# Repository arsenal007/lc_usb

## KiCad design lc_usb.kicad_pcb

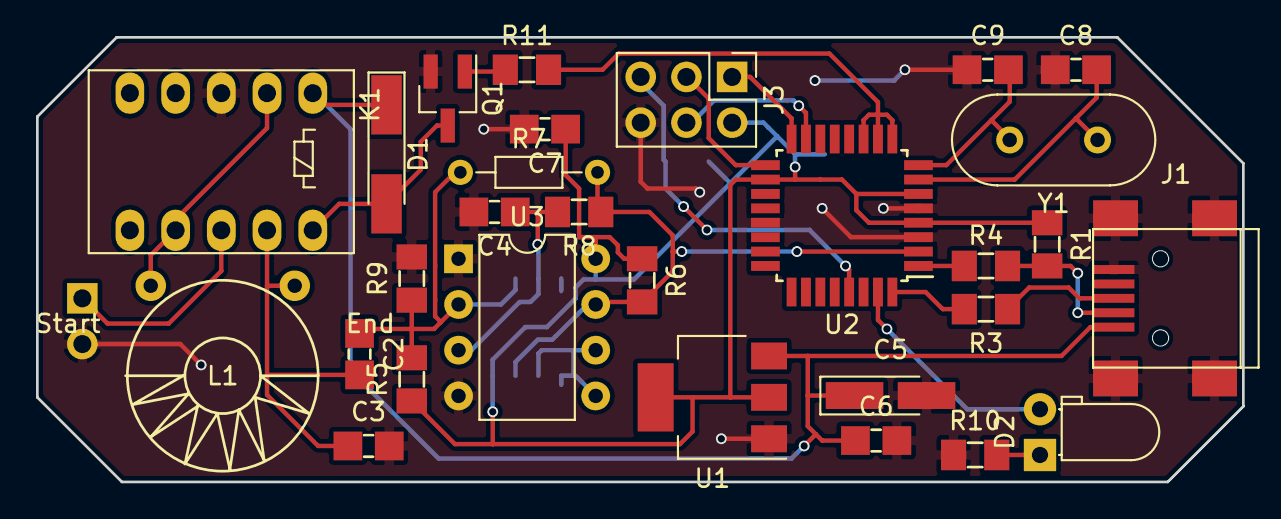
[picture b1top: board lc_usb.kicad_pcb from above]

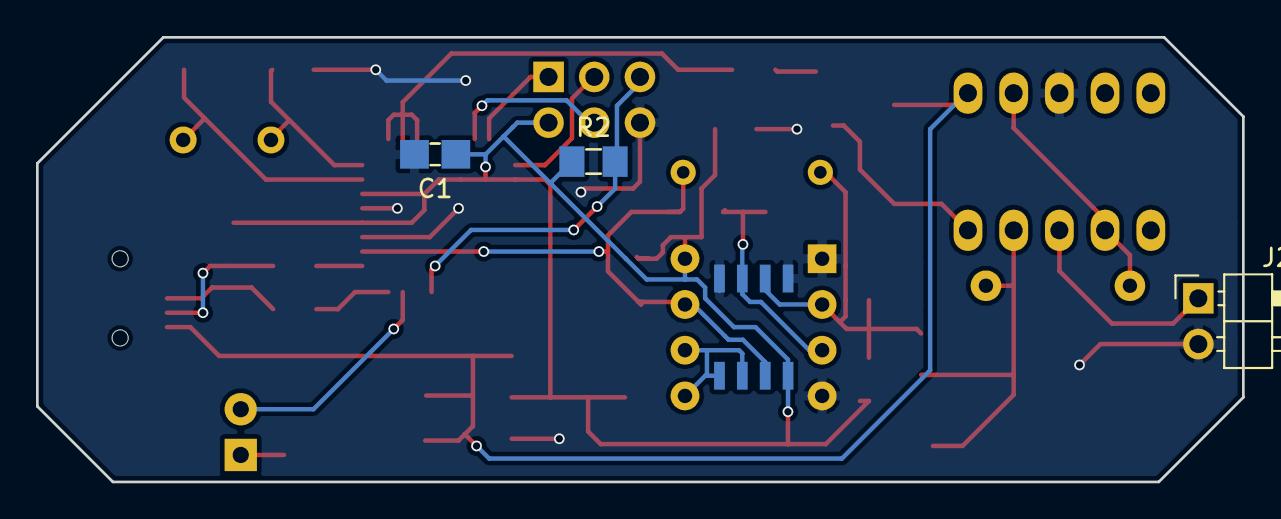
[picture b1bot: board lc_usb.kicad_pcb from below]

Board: 2 copper layers, 67.0 x 24.7 mm, 32 parts (3 on the bottom side), 25 nets.

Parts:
C1, C6: 100nF; C_1206_0603
C2, C4, C7: 1uF; C_1206_0603
C3: 1000; C_1206_0603
C5: 22uF; CP_Tantalum_Case-A_EIA-3216-18_Hand
C8, C9: 22; C_1206_0603
D1: LL4148; D_MiniMELF_Handsoldering
D2: LED; LED_D3.0mm_Horizontal_O1.27mm_Z6.0mm
J1: USB_B_Mini; USB_Mini-B
J2: Conn_01x02; Pin_Header_Angled_1x02_Pitch2.54mm
J3: SPI; Pin_Header_Straight_2x03_Pitch2.54mm
K1: FRT5; Relay_DPDT_FRT5
L1: 100uH; Choke_Toroid_horizontal_Diameter10-5mm_Amidon-T37
Q1: BC817; SOT-23_Handsoldering
R1, R2: 2.2k; R_1206_0603
R3, R4, R10, R11: 220; R_1206_0603
R5, R9: 100k; R_1206_0603
R6: 1k; R_1206_0603
R7: 100k; R_Axial_DIN0204_L3.6mm_D1.6mm_P7.62mm_Horizontal
R8: 47k; R_1206_0603
U1: AP1117-33; SOT-223-3_TabPin2
U2: ATMEGA8-16AU; TQFP-32_7x7mm_Pitch0.8mm
U3: LM311; DIP-8_SOIC-8_W7.62mm
Y1: 12Mhz; Crystal_HC49-U_Vertical

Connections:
/MISO: J3.1, U2.16
/MOSI: J3.4, U2.15
/RESET: J3.5, R2.2, U2.29
/SCK: J3.3, U2.17
GND: C1.2, C3.2, C4.2, C5.2, C6.2, C7.2, C8.1, C9.1, J1.5, J1.6, J2.2, J3.6, K1.3, Q1.2, R9.2, R10.1, U1.1, U2.3, U2.5, U2.21, U3.1, U3.4
L_C: D1.2, K1.10, Q1.3
unnamed: C1.1, C7.1, J3.2, R1.1, R2.1, R5.1, R6.1, U1.2, U2.4, U2.6, U2.18, U3.8
unnamed: C2.1, R5.2, R7.1, R9.1, U3.2
unnamed: C2.2, C3.1, K1.9, L1.2
unnamed: C4.1, R8.2, U3.3
unnamed: C5.1, C6.1, D1.1, J1.1, K1.1, U1.3
unnamed: C8.2, U2.7, Y1.1
unnamed: C9.2, U2.8, Y1.2
unnamed: D2.1, R10.2
unnamed: D2.2, U2.31
unnamed: J1.2, R1.2, R4.1
unnamed: J1.3, R3.1
unnamed: J2.1, K1.8
unnamed: K1.2, K1.7, L1.1
unnamed: Q1.1, R11.1
unnamed: R3.2, U2.32
unnamed: R4.2, U2.1
unnamed: R6.2, R7.2, R8.1, U2.2, U3.7
unnamed: R11.2, U2.9, U2.10, U2.11
unnamed: U3.5, U3.6

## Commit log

2019-03-23 minor changes
2019-03-23 own library
2019-03-25 Gerber,HOST Program LC2.1
2019-06-30 Add Qt application source code
2019-07-18 lambda function at remove tabs
